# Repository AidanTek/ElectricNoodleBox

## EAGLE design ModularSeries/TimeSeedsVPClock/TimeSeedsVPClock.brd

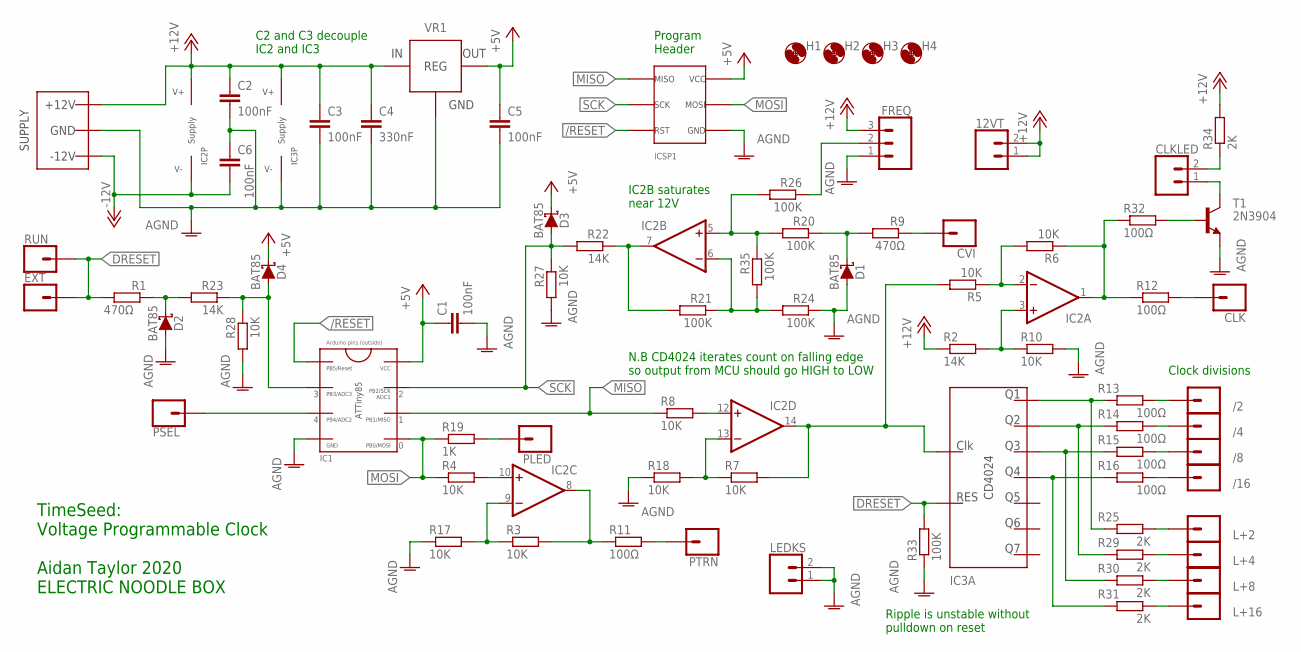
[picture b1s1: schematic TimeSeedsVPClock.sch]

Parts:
12VT: 2XWIREPAD; 1X02
/2, /4, /8, /16: 1XWIREPAD; 1X01
C1, C2, C3, C5, C6: 100nF; C050-025X075
C4: 330nF; C050-025X075
CLK: 1XWIREPAD; 1X01
CLKLED: 2XWIREPAD; 1X02
CVI: 1XWIREPAD; 1X01
D1, D2, D3, D4: BAT85; DO35-7
EXT: 1XWIREPAD; 1X01
FREQ: 3XWIREPAD; 1X03
H1, H2, H3, H4: MOUNT-HOLE3.2; 3,2
IC1: ATTINY2/4/85; DIL08
IC2: LM324; DIL14
IC3: CD4024BDIL; DIL14
ICSP1: ICSP_2.54; 2X3
L+2, L+4, L+8, L+16: 1XWIREPAD; 1X01
LEDKS: 2XWIREPAD; 1X02
PLED: 1XWIREPAD; 1X01
PSEL: 1XWIREPAD; 1X01
PTRN: 1XWIREPAD; 1X01
R1, R9: 470Ω; 0207/10
R2, R22, R23: 14K; 0207/10
R3, R4, R5, R6, R7, R8, R10, R17, R18, R27, R28: 10K; 0207/10
R11, R12, R13, R14, R15, R16, R32: 100Ω; 0207/10
R19: 1K; 0207/10
R20, R21, R24, R26, R33, R35: 100K; 0207/10
R25, R29, R30, R31, R34: 2K; 0207/10
RUN: 1XWIREPAD; 1X01
T1: 2N3904; TO92
VR1: L78L05TO92; TO92
WP1: COMBO_SUPPLY_HEADER; COMBINED_POWER

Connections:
+5V: C1.1, C5.1, D3.C, D4.C, IC1.8 (VCC), ICSP1.2 (6VCC), VR1.1 (VOUT)
+12V: 12VT.1, 12VT.2, C2.1, C3.1, C4.1, FREQ.3, IC2.4 (V+), IC3.14 (V+), R2.1, R34.2, VR1.3 (VIN), WP1.V+1 (V++), WP1.V+2 (V++), WP1.V+3 (V++)
-12V: C6.2, IC2.11 (V-), WP1.V-1 (V--), WP1.V-2 (V--), WP1.V-3 (V--)
/RESET: IC1.1 (RESET), ICSP1.5 (3RST)
AGND: C1.2, C2.2, C3.2, C4.2, C5.2, C6.1, D1.A, D2.A, FREQ.1, IC1.4 (GND), IC3.7 (V-), ICSP1.6 (4GND), LEDKS.1, LEDKS.2, R10.2, R17.1, R18.1, R24.1, R27.2, R28.2, R33.1, T1.3 (E), VR1.2 (GND), WP1.GND1 (AGND), WP1.GND2 (AGND), WP1.GND3 (AGND), WP1.GND4 (AGND), WP1.GND5 (AGND), WP1.GND6 (AGND), WP1.GND7 (AGND), WP1.GND8 (AGND)
DRESET: EXT.1, IC3.2 (RESET), R1.2, R33.2, RUN.1
MISO: IC1.6 (PB1), ICSP1.1 (1MISO), R8.1
MOSI: IC1.5 (PB0), ICSP1.4 (5MOSI), R4.1, R19.1
unnamed: D1.C, R9.2, R20.1
unnamed: CVI.1, R9.1
unnamed: IC2.10 (+IN), R4.2
unnamed: IC2.9 (-IN), R3.1, R17.2
unnamed: IC2.2 (-IN), R5.1, R6.2
unnamed: D2.C, R1.1, R23.2
unnamed: IC2.12 (+IN), R8.2
unnamed: PLED.1, R19.2
unnamed: IC2.8 (OUT), R3.2, R11.1
unnamed: PTRN.1, R11.2
unnamed: IC2.1 (OUT), R6.1, R12.1, R32.1
unnamed: IC3.12 (Q1), R13.1, R25.1
unnamed: IC3.11 (Q2), R14.1, R29.1
unnamed: IC3.9 (Q3), R15.1, R30.1
unnamed: IC3.6 (Q4), R16.1, R31.1
unnamed: L+2.1, R25.2
unnamed: L+4.1, R29.2
unnamed: L+8.1, R30.2
unnamed: IC2.5 (+IN), R20.2, R26.2, R35.1
unnamed: IC2.7 (OUT), R21.2, R22.1
unnamed: IC2.3 (+IN), R2.2, R10.1
unnamed: CLK.1, R12.2
unnamed: IC1.3 (PB4), PSEL.1
unnamed: IC2.6 (-IN), R21.1, R24.2, R35.2
unnamed: CLKLED.2, R34.1
unnamed: FREQ.2, R26.1
unnamed: IC2.13 (-IN), R7.1, R18.2
unnamed: /2.1, R13.2
unnamed: /4.1, R14.2
unnamed: /8.1, R15.2
unnamed: /16.1, R16.2
unnamed: IC2.14 (OUT), IC3.1 (CLK), R5.2, R7.2
unnamed: L+16.1, R31.2
unnamed: CLKLED.1, T1.1 (C)
unnamed: R32.2, T1.2 (B)
NOTRES: D4.A, IC1.2 (PB3), R23.1, R28.1
SCK: D3.A, IC1.7 (PB2), ICSP1.3 (2SCK), R22.2, R27.1

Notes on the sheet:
Program Header
C2 and C3 decouple IC2 and IC3
Clock divisions
TimeSeed: Voltage Programmable Clock Aidan Taylor 2020 ELECTRIC NOODLE BOX
IC2B saturates near 12V
Ripple is unstable without pulldown on reset
N.B CD4024 iterates count on falling edge so output from MCU should go HIGH to LOW

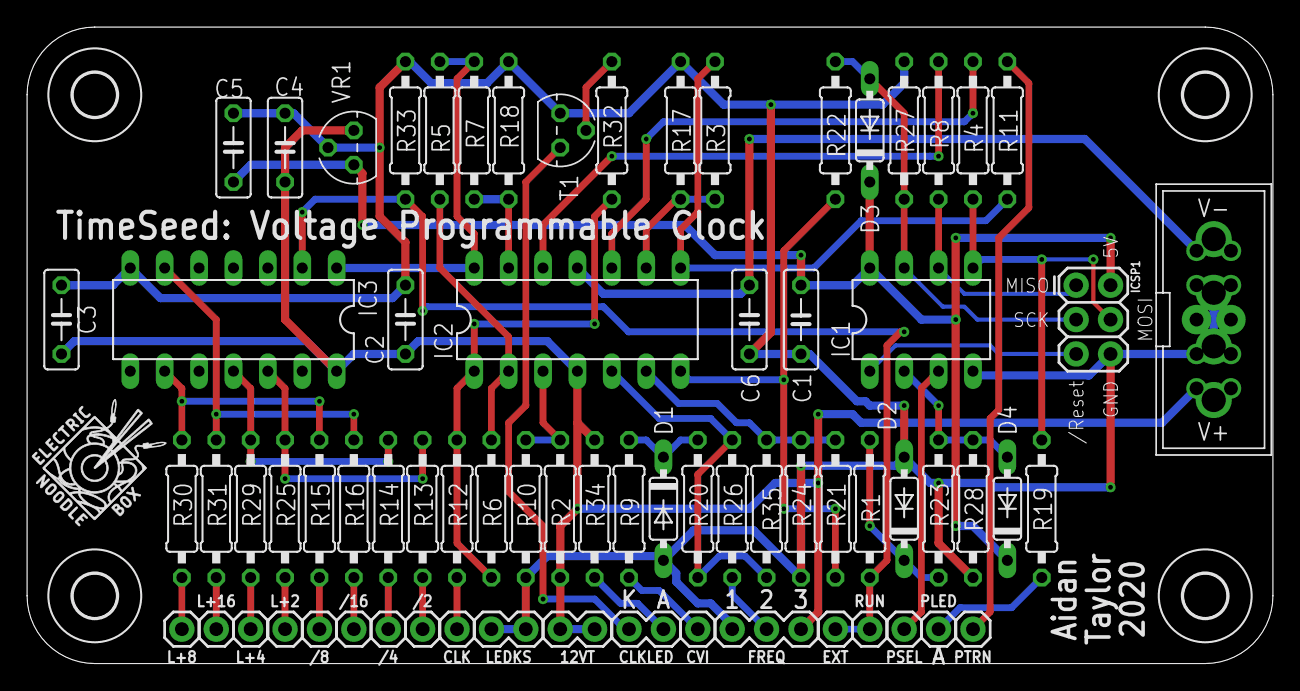
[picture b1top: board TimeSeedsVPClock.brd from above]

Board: 2 copper layers, 92.0 x 47.0 mm, 77 parts (1 on the bottom side), 45 nets.

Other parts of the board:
U$1, U$2: LOGO10X10

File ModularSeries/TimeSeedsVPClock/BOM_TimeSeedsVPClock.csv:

Qty,Value,Package,Parts,Description,Retailer,Catalogue
,,,,,,
5,100K,0207/10,"R20, R21, R24, R26, R33",RESISTOR 1/4W,Farnell,2329853
7,100Ω,0207/10,"R11, R12, R13, R14, R15, R16, R32",RESISTOR 1/4W,Farnell,2329854
9,10K,0207/10,"R4, R5, R6, R8, R10, R17, R18, R27, R28",RESISTOR 1/4W,Farnell,2329855
3,14K,0207/10,"R2, R22, R23",RESISTOR 1/4W,Farnell,1563095
1,1K,0207/10,"R34",RESISTOR 1/4W,Farnell,2329885
2,20K,0207/10,"R3, R7",RESISTOR 1/4W,Farnell,2329897
7,470Ω,0207/10,"R1, R9, R19, R25, R29, R30, R31",RESISTOR 1/4W,Farnell,2329942
,,,,,,
5,100nF,C050-025X075,"C1, C2, C3, C5, C6",CAPACITOR,Farnell,2797801
1,330nF,C050-025X075,C4,CAPACITOR,Farnell,2990808
,,,,,,
4,BAT85,DO35-7,"D1, D2, D3, D4",BAT85 Schottky Diode,Farnell,2889133
1,2N3904,TO92,T1,NPN TRANSISTOR TO-92 package,Farnell,1574370
1,L78L05,TO92,VR1,L78L05 TO-92 package,Farnell,3335816
1,ATTiny85,DIL08,IC1,ATTiny85 8 pin DIL,Farnell,1455162
1,CD4024,DIL14,IC3,CD4024 14 pin DIL,Farnell,1470783
1,TL084_DIP,DIL14,IC2,TL084 14 pin DIL,Farnell,3117825
,,,,,,
6,LED,5mm LED,"CLKLED, L+2, L+4, L+8, L+16, PLED",LED (panel part),Farnell,1581143
8,Banana Connector,,"/2, /4, /8, /16, CLK, CVI, EXT, PTRN",Banana or Jack patch point (panel part),Farnell,1698951
2,B100K,,"CVI, FREQ",Taiwan Alpha 16mm (panel part),Rapid,65-0756
2,Push button,,"RUN, PSEL",Momentary push button (panel part),Farnell,1634691
1,Power Header,,WP1,4 way MTA156 or 10 way IDC,Farnell,589068
1,(Alt) Power Header,,WP1,10 way Shrouded IDC,Farnell,2843527

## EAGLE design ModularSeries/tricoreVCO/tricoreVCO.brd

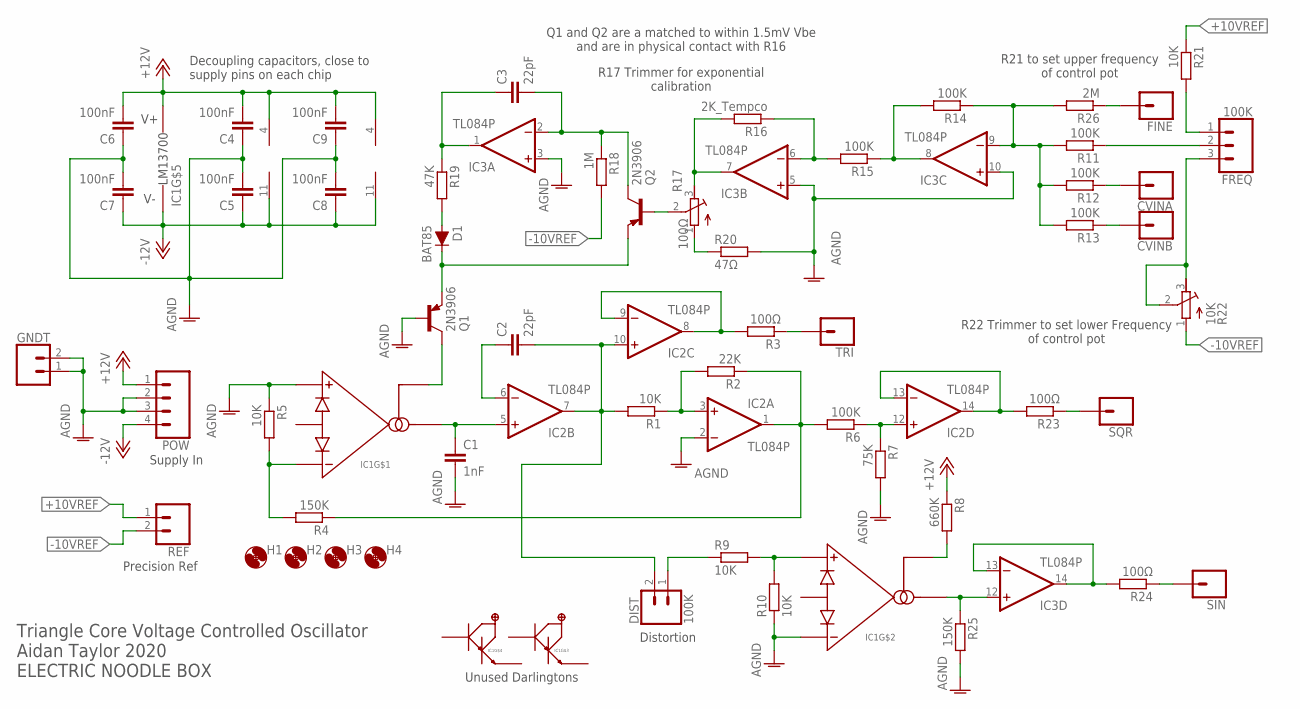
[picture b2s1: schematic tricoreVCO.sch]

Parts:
C1: 1nF; C050-025X075
C2, C3: 22pF; C050-025X075
C4, C5, C6, C7, C8, C9: 100nF; C050-025X075
CVINA: CONN_01; 1X01
CVINB: CONN_01; 1X01
D1: BAT85; DIODE-1N4148
DIST: 100K; 1X02
FINE: CONN_01; 1X01
FREQ: 100K; 1X03
GNDT: CONN_02; 1X02
H1, H2, H3, H4: MOUNT-HOLE3.2; 3,2
IC1: LM13700_DIP; DIP16
IC2, IC3: TL084P; DIL14
POW: CONN_04POLAR; MOLEX-1X4
Q1, Q2: 2N3906; TO92
R1, R5, R9, R10, R21: 10K; 0207/10
R2: 22K; 0207/10
R3, R23, R24: 100Ω; 0207/10
R4, R25: 150K; 0207/10
R6, R11, R12, R13, R14, R15: 100K; 0207/10
R7: 75K; 0207/10
R8: 660K; 0207/10
R16: 2K_Tempco; 0207/10
R17: 100Ω; RTRIM3296W
R18: 1M; 0207/10
R19: 47K; 0207/10
R20: 47Ω; 0207/10
R22: 10K; RTRIM3296W
R26: 2M; 0207/10
REF: CONN_02POLAR; MOLEX-1X2
SIN: CONN_01; 1X01
SQR: CONN_01; 1X01
TRI: CONN_01; 1X01

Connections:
+10VREF: R21.1, REF.1
+12V: C4.2, C6.2, C9.2, IC1.11 (V+), IC2.4 (V+), IC3.4 (V+), POW.1, R8.1
-10VREF: R18.2, R22.1 (A), REF.2
-12V: C5.1, C7.1, C8.1, IC1.6 (V-), IC2.11 (V-), IC3.11 (V-), POW.4
AGND: C1.2, C4.1, C5.2, C6.1, C7.2, C8.2, C9.1, GNDT.1, GNDT.2, IC1.3 (AMP+), IC1.13 (AMP-), IC2.2 (-IN), IC3.3 (+IN), IC3.5 (+IN), IC3.10 (+IN), POW.2, POW.3, Q1.2 (B), R5.1, R7.2, R10.1, R20.2, R25.2
unnamed: C2.1, IC2.6 (-IN)
unnamed: C2.2, DIST.2, IC2.7 (OUT), IC2.10 (+IN), R1.2
unnamed: IC2.3 (+IN), R1.1, R2.2
unnamed: C1.1, IC1.5 (AMPOUT), IC2.5 (+IN)
unnamed: IC2.1 (OUT), R2.1, R4.1, R6.2
unnamed: IC2.8 (OUT), IC2.9 (-IN), R3.2
unnamed: IC1.4 (AMP-), R4.2, R5.2
unnamed: IC1.14 (AMP+), R9.2, R10.2
unnamed: IC2.12 (+IN), R6.1, R7.1
unnamed: IC1.12 (AMPOUT), IC3.12 (+IN), R25.1
unnamed: IC1.16 (AMPBIAS), R8.2
unnamed: IC1.1 (AMPBIAS), Q1.1 (C)
unnamed: DIST.1, R9.1
unnamed: IC3.7 (OUT), R16.2, R17.3 (E)
unnamed: IC3.6 (-IN), R15.2, R16.1
unnamed: IC3.8 (OUT), R14.2, R15.1
unnamed: Q2.2 (B), R17.2 (S)
unnamed: C3.2, IC3.2 (-IN), Q2.1 (C), R18.1
unnamed: R17.1 (A), R20.1
unnamed: C3.1, IC3.1 (OUT), R19.1
unnamed: D1.C, Q1.3 (E), Q2.3 (E)
unnamed: D1.A, R19.2
unnamed: IC3.9 (-IN), R11.2, R12.2, R13.2, R14.1, R26.2
unnamed: FREQ.2, R11.1
unnamed: FREQ.3, R22.2 (S), R22.3 (E)
unnamed: FREQ.1, R21.2
unnamed: CVINA.1, R12.1
unnamed: CVINB.1, R13.1
unnamed: R3.1, TRI.1
unnamed: R23.1, SQR.1
unnamed: R24.1, SIN.1
unnamed: FINE.1, R26.1
SINE_OUT: IC3.13 (-IN), IC3.14 (OUT), R24.2
SQUARE_OUT: IC2.13 (-IN), IC2.14 (OUT), R23.2

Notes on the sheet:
Distortion
Unused Darlingtons
R22 Trimmer to set lower Frequency of control pot
R17 Trimmer for exponential calibration
R21 to set upper frequency of control pot
Q1 and Q2 are a matched to within 1.5mV Vbe and are in physical contact with R16
Triangle Core Voltage Controlled Oscillator Aidan Taylor 2020 ELECTRIC NOODLE BOX
Supply In
Precision Ref
Decoupling capacitors, close to supply pins on each chip

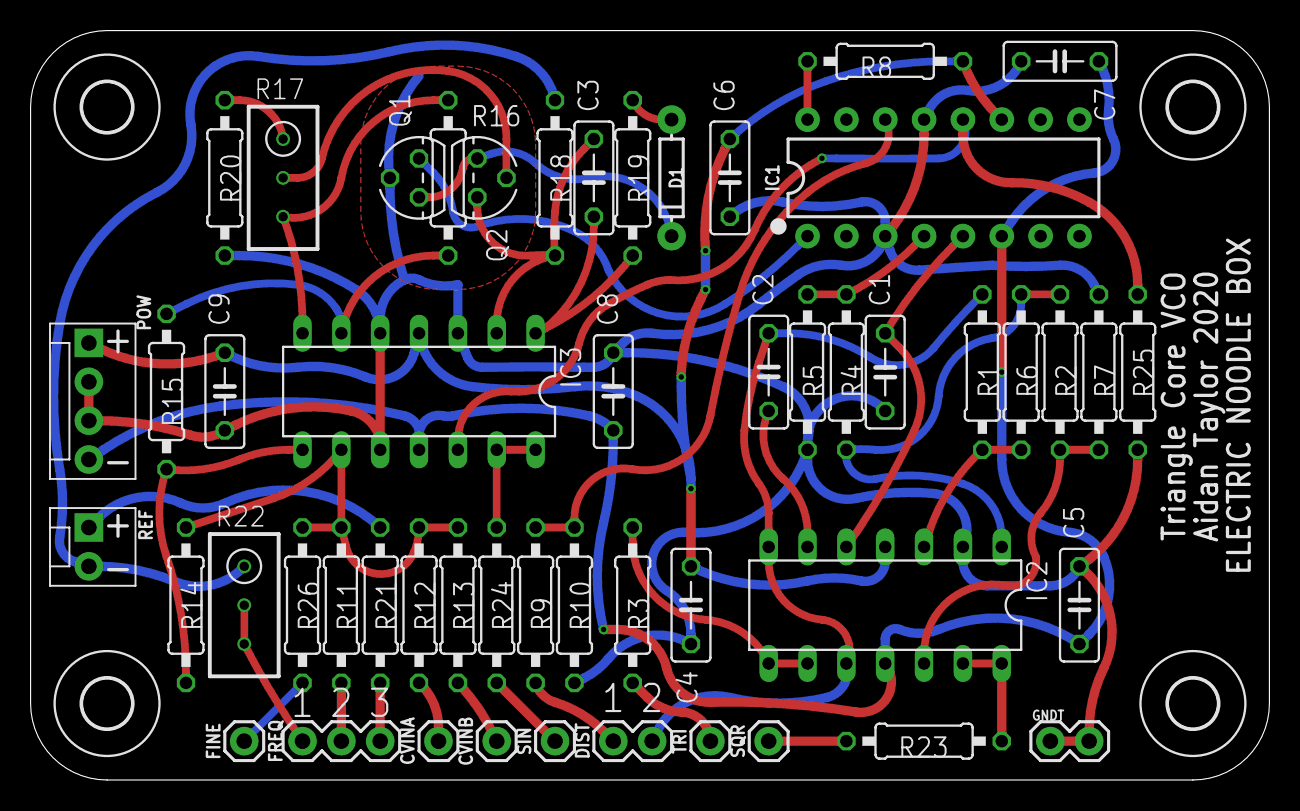
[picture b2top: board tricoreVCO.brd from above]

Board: 2 copper layers, 81.0 x 49.0 mm, 56 parts (0 on the bottom side), 39 nets.

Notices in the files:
parts and their libraries:
SparkFun-Connectors: Licensing: Creative Commons ShareAlike 4.0 International - https://creativecommons.org/licenses/by-sa/4.0
